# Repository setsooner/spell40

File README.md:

<div align=center>
  
</div>

---

<h4 align="center">A megumin themed 40% (but not really) keyboard.</h4>
<div align="center">
  
</div>

## Intro
hello! spell40 is a 40% keyboard with a layout reminiscent of the W1-AT. It was designed by me and my friend binb0y of mkh. The board utlizes tadpole + gummy oring mounts, and a 6.2deg typing angle. The engravings (and general design, to an extent) are inspired by konosuba! character megumin. The layout is inspired by both the W1-AT, as well as the mkh studio bully. We took the numpad and xt from the W1 and attached it to the 13.5u width of the bully, with completely different bottom row support. The board should be compatible with the majority of base kits, given it includes the numpad. 

As of time of writing, prototype 1 has been received, and faults in the design have been found and remedied. A second prototype run is in the works. Hotswap pcb is basically done, but I will not be posting it until I've verified it works.

## Required Components
* Daughterboard
  * spell is designed to use any C series daughterboard, but the 3D model of [this](https://github.com/Unified-Daughterboard/UDB-C-JSH) was what I used while modeling.
* Mounting
  * spell mounts with either 9 GEON tadpoles, or with an o-ring. O-ring specs are 3.5mm CS x 200m ID. O-ring of 192mm has been tested and verified to work. TKL orings also work.
  * [Tadpoles](https://geon.works/products/tadpole)
  * [Where we're getting our o-ring](https://www.polymax.co.uk/o-rings/rubber-silicone-o-rings/)
* Screws
  * Case screws are M2x8mm, daughterboard screws are M2x4mm.
* PCB
  * TODO: put text here.
* Case Feet
  * spell uses [SKUF feet](https://github.com/Zambumon/SKUF).

## Special Thanks 
While I say me and binb0y designed this, it took a lot of help from the community to get here. I'd like to extend my thanks to chill for his invaluable PCB advice. zhol and paaradiso of mkh for general design advice for everything from pcbs to the specifics of bottom case engravings. GEON for some pointers on mounting point placement. Cute for making amazing renders, and everyone else in MechKeys who contributed their opinions and for dealing with our constant pestering over the 1.5 years it took for the project to get here.

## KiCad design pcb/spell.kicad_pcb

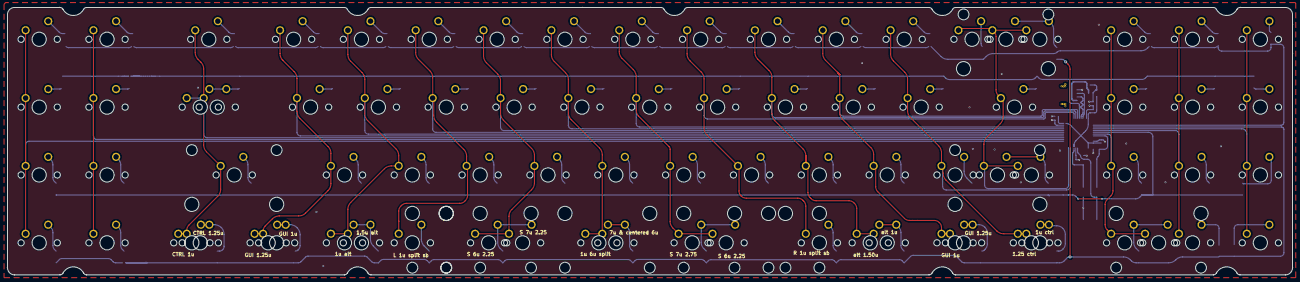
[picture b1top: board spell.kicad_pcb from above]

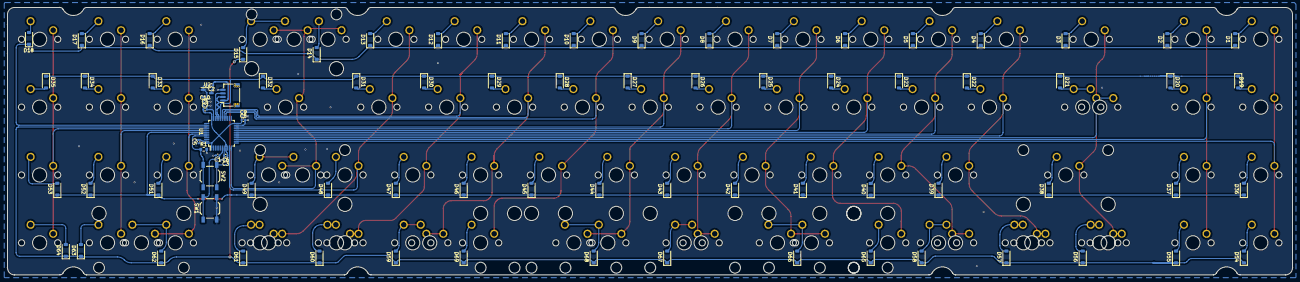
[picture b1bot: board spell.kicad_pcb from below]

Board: 2 copper layers, 360.8 x 75.1 mm, 175 parts (84 on the bottom side), 96 nets.

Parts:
C1, C5, C6, C7, C8: 100n; C_0402_1005Metric
C2, C3, C10: 1u; C_0402_1005Metric
C4: 4.7u; C_0402_1005Metric
C9: 10n; C_0402_1005Metric
D1, D2, D3, D4, D5, D6, D7, D8, D9, D10, D11, D12, D13, D14, D15, D16, D17, D18, D19, D20, D21, D22, D23, D24, D25, D26, D27, D28, D29, D30, D31, D32, D33, D34, D35, D36, D37, D38, D39, D40, D41, D42, D43, D44, D45, D46, D47, D48, D49, D51, D52, D53, D54, D55, D56, D57, D58, D59, D60, D61, D62, D63, D64, D65, D66, D67, D68, D69: D; D_SOD-123
J1: JST SH 4p; JST_SH_SM04B-SRSS-TB_1x04-1MP_P1.00mm_Horizontal
MX1: F1; SW_MX_1u
MX2: F5; SW_MX_1u
MX3: TAB; SW_MX_1.5u
MX4: Q; SW_MX_1u
MX5: W; SW_MX_1u
MX6: E; SW_MX_1u
MX7: R; SW_MX_1u
MX8: T; SW_MX_1u
MX9: Y; SW_MX_1u
MX10: U; SW_MX_1u
MX11: I; SW_MX_1u
MX12: O; SW_MX_1u
MX13: P; SW_MX_1u
MX14: [; SW_MX_1u
MX15: ]; SW_MX_1u
MX16: BS; SW_MX_1u
MX17: 7; SW_MX_1u
MX18: 8; SW_MX_1u
MX19: 9; SW_MX_1u
MX20: F2; SW_MX_1u
MX21: F6; SW_MX_1u
MX22: CL; SW_MX_1.75u
MX23: A; SW_MX_1u
MX24: S; SW_MX_1u
MX25: D; SW_MX_1u
MX26: F; SW_MX_1u
MX27: G; SW_MX_1u
MX28: H; SW_MX_1u
MX29: J; SW_MX_1u
MX30: K; SW_MX_1u
MX31: L; SW_MX_1u
MX32: ;; SW_MX_1u
MX33: Enter; SW_MX_1.75u
MX34: 4; SW_MX_1u
MX35: 5; SW_MX_1u
MX36: 6; SW_MX_1u
MX37: F3; SW_MX_1u
MX38: F7; SW_MX_1u
MX39: LS; SW_MX_1u
MX40: Z; SW_MX_1u
MX41: X; SW_MX_1u
MX42: C; SW_MX_1u
MX43: V; SW_MX_1u
MX44: B; SW_MX_1u
MX45: N; SW_MX_1u
MX46: M; SW_MX_1u
MX47, MX65, MX66: .; SW_MX_1u
MX48: ,; SW_MX_1u
MX49: /; SW_MX_1u
MX50: Shift 1.25; SW_MX_1.25u
MX51: Shift 2.25u; SW_MX_1u
MX52: 1; SW_MX_1u
MX53: 2; SW_MX_1u
MX54: 3; SW_MX_1u
MX55: F4; SW_MX_1u
MX56: F8; SW_MX_1u
MX57: CTRL 1u; SW_MX_1u
MX58, MX61: GUI 1.25u; SW_MX_1.25u
MX59: 1u alt; SW_MX_1u
MX60: alt 1u; SW_MX_1u
MX62: 1u ctrl; SW_MX_1u
MX63: 0; SW_MX_1u
MX64: 2u 0; SW_MX_1u
MX67: alt 1.50u; SW_MX_1.5u
MX68, MX71: GUI 1u; SW_MX_1u
MX69: 1.25 ctrl; SW_MX_1.25u
MX70: CTRL 1.25u; SW_MX_1.25u
MX72: 1.5u alt; SW_MX_1.5u
MX73: L 1u split sb; SW_MX_1u
MX74: S 7u 2.25; SW_MX_1u
MX75: 7u & centered 6u; SW_MX_1u
MX76: S 7u 2.75; SW_MX_1u
MX77: R 1u split sb; SW_MX_1u
MX78, MX80: S 6u 2.25; SW_MX_1u
MX79: 1u 6u split; SW_MX_1u
MX81: CL; SW_MX_1.25u
R1: 10k; R_0603_1608Metric
S1, S2: 2u; STAB_MX_2u
S3, S7, S11, S12: 2.25; STAB_MX_2.25u
S5, S8: 2.75; STAB_MX_2.75u
S9: 7u; STAB_MX_7u
S10: 6u; STAB_MX_6u
SW1: RST; SW_SPST_TL3342
SW2: BOOT; SW_SPST_TL3342
U1: STM32F072CBTx; LQFP-48_7x7mm_P0.5mm
U2: XC6206PxxxMR; SOT-23-3

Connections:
+3V3: C3.1, C4.1, C5.1, C6.1, C7.1, C8.1, C9.1, C10.1, SW2.1, U1.1 (VBAT), U1.9 (VDDA), U1.24 (VDD), U1.36 (VDDIO2), U1.48 (VDD), U2.2 (VO)
+5V: C2.1, J1.1, U2.3 (VI)
BOOT0: R1.1, SW2.2, U1.44 (BOOT0)
COL01: MX1.1, MX20.1, MX37.1, MX55.1, U1.14 (PA4)
COL02: MX2.1, MX21.1, MX38.1, MX56.1, U1.15 (PA5)
COL03: MX3.1, MX22.1, MX39.1, MX57.1, MX70.1, MX81.1, U1.16 (PA6)
COL04: MX4.1, MX23.1, MX40.1, MX58.1, MX71.1, U1.17 (PA7)
COL05: MX5.1, MX24.1, MX41.1, MX59.1, MX72.1, U1.18 (PB0)
COL06: MX6.1, MX25.1, MX42.1, MX73.1, U1.19 (PB1)
COL07: MX7.1, MX26.1, MX43.1, MX74.1, MX78.1, U1.20 (PB2)
COL08: MX8.1, MX27.1, MX44.1, MX75.1, MX79.1, U1.21 (PB10)
COL09: MX9.1, MX28.1, MX45.1, MX76.1, MX80.1, U1.22 (PB11)
COL10: MX10.1, MX29.1, MX46.1, MX77.1, U1.28 (PB15)
COL11: MX11.1, MX30.1, MX47.1, MX60.1, MX67.1, U1.29 (PA8)
COL12: MX12.1, MX31.1, MX48.1, MX61.1, MX68.1, U1.30 (PA9)
COL13: MX13.1, MX32.1, MX49.1, MX62.1, MX69.1, U1.11 (PA1)
COL14: MX14.1, MX15.1, MX16.1, MX33.1, MX50.1, MX51.1, U1.12 (PA2)
COL15: MX17.1, MX34.1, MX52.1, MX63.1, MX64.1, U1.43 (PB7)
COL16: MX18.1, MX35.1, MX53.1, MX65.1, U1.41 (PB5)
COL17: MX19.1, MX36.1, MX54.1, MX66.1, U1.40 (PB4)
D+: J1.3, U1.33 (PA12)
D-: J1.2, U1.32 (PA11)
GND: C1.2, C2.2, C3.2, C4.2, C5.2, C6.2, C7.2, C8.2, C9.2, C10.2, J1.4, R1.2, SW1.2, U1.8 (VSSA), U1.23 (VSS), U1.35 (VSS), U1.47 (VSS), U2.1 (GND)
unnamed: D1.2 (A), MX1.2
unnamed: D2.2 (A), MX2.2
unnamed: D3.2 (A), MX3.2
unnamed: D4.2 (A), MX4.2
unnamed: D5.2 (A), MX5.2
unnamed: D6.2 (A), MX6.2
unnamed: D7.2 (A), MX7.2
unnamed: D8.2 (A), MX8.2
unnamed: D9.2 (A), MX9.2
unnamed: D10.2 (A), MX10.2
unnamed: D11.2 (A), MX11.2
unnamed: D12.2 (A), MX12.2
unnamed: D13.2 (A), MX13.2
unnamed: D14.2 (A), MX14.2
unnamed: D15.2 (A), MX15.2, MX16.2
unnamed: D16.2 (A), MX17.2
unnamed: D17.2 (A), MX18.2
unnamed: D18.2 (A), MX19.2
unnamed: D19.2 (A), MX20.2
unnamed: D20.2 (A), MX21.2
unnamed: D21.2 (A), MX22.2, MX81.2
unnamed: D22.2 (A), MX23.2
unnamed: D23.2 (A), MX24.2
unnamed: D24.2 (A), MX25.2
unnamed: D25.2 (A), MX26.2
unnamed: D26.2 (A), MX27.2
unnamed: D27.2 (A), MX28.2
unnamed: D28.2 (A), MX29.2
unnamed: D29.2 (A), MX30.2
unnamed: D30.2 (A), MX31.2
unnamed: D31.2 (A), MX32.2
unnamed: D32.2 (A), MX33.2
unnamed: D33.2 (A), MX34.2
unnamed: D34.2 (A), MX35.2
unnamed: D35.2 (A), MX36.2
unnamed: D36.2 (A), MX37.2
unnamed: D37.2 (A), MX38.2
unnamed: D38.2 (A), MX39.2
unnamed: D39.2 (A), MX40.2
unnamed: D40.2 (A), MX41.2
unnamed: D41.2 (A), MX42.2
unnamed: D42.2 (A), MX43.2
unnamed: D43.2 (A), MX44.2
unnamed: D44.2 (A), MX45.2
unnamed: D45.2 (A), MX46.2
unnamed: D46.2 (A), MX47.2
unnamed: D47.2 (A), MX48.2
unnamed: D48.2 (A), MX49.2
unnamed: D49.2 (A), MX50.2, MX51.2
unnamed: D51.2 (A), MX52.2
unnamed: D52.2 (A), MX53.2
unnamed: D53.2 (A), MX54.2
unnamed: D54.2 (A), MX55.2
unnamed: D55.2 (A), MX56.2
unnamed: D56.2 (A), MX57.2, MX70.2
unnamed: D57.2 (A), MX58.2, MX71.2
unnamed: D58.2 (A), MX59.2, MX72.2
unnamed: D59.2 (A), MX60.2, MX67.2
unnamed: D60.2 (A), MX61.2, MX68.2
unnamed: D61.2 (A), MX62.2, MX69.2
unnamed: D62.2 (A), MX63.2, MX64.2
unnamed: D63.2 (A), MX65.2
unnamed: D64.2 (A), MX66.2
unnamed: D65.2 (A), MX73.2
unnamed: D66.2 (A), MX74.2, MX78.2
unnamed: D67.2 (A), MX75.2, MX79.2
unnamed: D68.2 (A), MX76.2, MX80.2
unnamed: D69.2 (A), MX77.2
ROW1: D1.1 (K), D2.1 (K), D3.1 (K), D4.1 (K), D5.1 (K), D6.1 (K), D7.1 (K), D8.1 (K), D9.1 (K), D10.1 (K), D11.1 (K), D12.1 (K), D13.1 (K), D14.1 (K), D16.1 (K), D17.1 (K), D18.1 (K), U1.38 (PA15)
ROW2: D19.1 (K), D20.1 (K), D21.1 (K), D22.1 (K), D23.1 (K), D24.1 (K), D25.1 (K), D26.1 (K), D27.1 (K), D28.1 (K), D29.1 (K), D30.1 (K), D31.1 (K), D32.1 (K), D33.1 (K), D34.1 (K), D35.1 (K), U1.31 (PA10)
ROW3: D36.1 (K), D37.1 (K), D38.1 (K), D39.1 (K), D40.1 (K), D41.1 (K), D42.1 (K), D43.1 (K), D44.1 (K), D45.1 (K), D46.1 (K), D47.1 (K), D48.1 (K), D49.1 (K), D51.1 (K), D52.1 (K), D53.1 (K), U1.42 (PB6)
ROW4: D15.1 (K), D54.1 (K), D55.1 (K), D56.1 (K), D57.1 (K), D58.1 (K), D59.1 (K), D60.1 (K), D61.1 (K), D62.1 (K), D63.1 (K), D64.1 (K), D65.1 (K), D66.1 (K), D67.1 (K), D68.1 (K), D69.1 (K), U1.39 (PB3)
~RST: C1.1, SW1.1, U1.7 (NRST)

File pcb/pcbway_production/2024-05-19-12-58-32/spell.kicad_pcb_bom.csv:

designator,quantity,value,pack,mpn,mount_type
", , , , , , , ",8,,,,tht
"C1, C5, C6, C7, C8",5,100n,C_0402_1005Metric,,smt
"C10, C2, C3",3,1u,C_0402_1005Metric,,smt
C4,1,4.7u,C_0402_1005Metric,,smt
C9,1,10n,C_0402_1005Metric,,smt
"D1, D10, D11, D12, D13, D14, D15, D16, D17, D18, D19, D2, D20, D21, D22, D23, D24, D25, D26, D27, D28, D29, D3, D30, D31, D32, D33, D34, D35, D36, D37, D38, D39, D4, D40, D41, D42, D43, D44, D45, D46, D47, D48, D49, D5, D51, D52, D53, D54, D55, D56, D57, D58, D59, D6, D60, D61, D62, D63, D64, D65, D66, D67, D68, D69, D7, D8, D9",68,D,D_SOD-123,,smt
J1,1,JST SH 4p,JST_SH_SM04B-SRSS-TB_1x04-1MP_P1.00mm_Horizontal,,smt
MX1,1,F1,SW_MX_1u,,tht
MX10,1,U,SW_MX_1u,,tht
MX11,1,I,SW_MX_1u,,tht
MX12,1,O,SW_MX_1u,,tht
MX13,1,P,SW_MX_1u,,tht
MX14,1,[,SW_MX_1u,,tht
MX15,1,],SW_MX_1u,,tht
MX16,1,BS,SW_MX_1u,,tht
MX17,1,7,SW_MX_1u,,tht
MX18,1,8,SW_MX_1u,,tht
MX19,1,9,SW_MX_1u,,tht
MX2,1,F5,SW_MX_1u,,tht
MX20,1,F2,SW_MX_1u,,tht
MX21,1,F6,SW_MX_1u,,tht
MX22,1,CL,SW_MX_1.75u,,tht
MX23,1,A,SW_MX_1u,,tht
MX24,1,S,SW_MX_1u,,tht
MX25,1,D,SW_MX_1u,,tht
MX26,1,F,SW_MX_1u,,tht
MX27,1,G,SW_MX_1u,,tht
MX28,1,H,SW_MX_1u,,tht
MX29,1,J,SW_MX_1u,,tht
MX3,1,TAB,SW_MX_1.5u,,tht
MX30,1,K,SW_MX_1u,,tht
MX31,1,L,SW_MX_1u,,tht
MX32,1,;,SW_MX_1u,,tht
MX33,1,Enter,SW_MX_1.75u,,tht
MX34,1,4,SW_MX_1u,,tht
MX35,1,5,SW_MX_1u,,tht
MX36,1,6,SW_MX_1u,,tht
MX37,1,F3,SW_MX_1u,,tht
MX38,1,F7,SW_MX_1u,,tht
MX39,1,LS,SW_MX_1u,,tht
MX4,1,Q,SW_MX_1u,,tht
MX40,1,Z,SW_MX_1u,,tht
MX41,1,X,SW_MX_1u,,tht
MX42,1,C,SW_MX_1u,,tht
MX43,1,V,SW_MX_1u,,tht
MX44,1,B,SW_MX_1u,,tht
MX45,1,N,SW_MX_1u,,tht
MX46,1,M,SW_MX_1u,,tht
"MX47, MX65, MX66",3,.,SW_MX_1u,,tht
MX48,1,",",SW_MX_1u,,tht
MX49,1,/,SW_MX_1u,,tht
MX5,1,W,SW_MX_1u,,tht
MX50,1,Shift 1.25,SW_MX_1.25u,,tht
MX51,1,Shift 2.25u,SW_MX_1u,,tht
MX52,1,1,SW_MX_1u,,tht
MX53,1,2,SW_MX_1u,,tht
MX54,1,3,SW_MX_1u,,tht
MX55,1,F4,SW_MX_1u,,tht
MX56,1,F8,SW_MX_1u,,tht
MX57,1,CTRL 1u,SW_MX_1u,,tht
"MX58, MX61",2,GUI 1.25u,SW_MX_1.25u,,tht
MX59,1,1u alt,SW_MX_1u,,tht
MX6,1,E,SW_MX_1u,,tht
MX60,1,alt 1u,SW_MX_1u,,tht
MX62,1,1u ctrl,SW_MX_1u,,tht
MX63,1,0,SW_MX_1u,,tht
MX64,1,2u 0,SW_MX_1u,,tht
MX67,1,alt 1.50u,SW_MX_1.5u,,tht
"MX68, MX71",2,GUI 1u,SW_MX_1u,,tht
MX69,1,1.25 ctrl,SW_MX_1.25u,,tht
MX7,1,R,SW_MX_1u,,tht
MX70,1,CTRL 1.25u,SW_MX_1.25u,,tht
MX72,1,1.5u alt,SW_MX_1.5u,,tht
MX73,1,L 1u split sb,SW_MX_1u,,tht
MX74,1,S 7u 2.25,SW_MX_1u,,tht
MX75,1,7u & centered 6u,SW_MX_1u,,tht
MX76,1,S 7u 2.75,SW_MX_1u,,tht
MX77,1,R 1u split sb,SW_MX_1u,,tht
"MX78, MX80",2,S 6u 2.25,SW_MX_1u,,tht
MX79,1,1u 6u split,SW_MX_1u,,tht
MX8,1,T,SW_MX_1u,,tht
MX81,1,CL,SW_MX_1.25u,,tht
MX9,1,Y,SW_MX_1u,,tht
R1,1,10k,R_0603_1608Metric,,smt
"S1, S2",2,2u,STAB_MX_2u,,tht
S10,1,6u,STAB_MX_6u,,tht
"S11, S12, S3, S7",4,2.25,STAB_MX_2.25u,,tht
"S5, S8",2,2.75,STAB_MX_2.75u,,tht
S9,1,7u,STAB_MX_7u,,tht
SW1,1,RST,SW_SPST_TL3342,,smt
SW2,1,BOOT,SW_SPST_TL3342,,smt
U1,1,STM32F072CBTx,LQFP-48_7x7mm_P0.5mm,,smt
U2,1,XC6206PxxxMR,SOT-23-3,,smt

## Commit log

2024-05-16 added pcb stuff
2024-05-16 added things
2024-05-16 added edge cuts
2024-05-19 update to latest
2024-05-19 moar updates
2024-05-19 got rid of uneeded files
2024-07-10 updated files to proto production
2024-07-10 added images because free image hosters suck
2024-08-07 updated to match proto r2
